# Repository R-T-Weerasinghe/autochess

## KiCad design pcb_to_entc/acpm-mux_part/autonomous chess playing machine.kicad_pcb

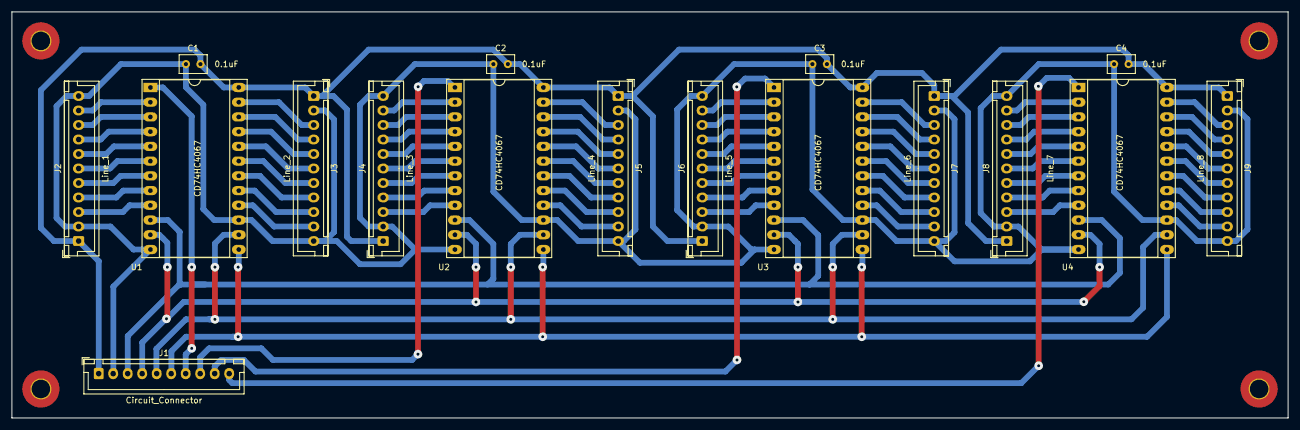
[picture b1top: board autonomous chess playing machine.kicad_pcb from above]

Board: 2 copper layers, 220.0 x 70.0 mm, 17 parts (0 on the bottom side), 74 nets.

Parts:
C1, C2, C3, C4: 0.1uF; C_Rect_L4.6mm_W3.0mm_P2.50mm_MKS02_FKP02
J1: Circuit_Connector; JST_XH_B10B-XH-A_1x10_P2.50mm_Vertical
J2: Line_1; JST_XH_B11B-XH-A_1x11_P2.50mm_Vertical
J3: Line_2; JST_XH_B11B-XH-A_1x11_P2.50mm_Vertical
J4: Line_3; JST_XH_B11B-XH-A_1x11_P2.50mm_Vertical
J5: Line_4; JST_XH_B11B-XH-A_1x11_P2.50mm_Vertical
J6: Line_5; JST_XH_B11B-XH-A_1x11_P2.50mm_Vertical
J7: Line_6; JST_XH_B11B-XH-A_1x11_P2.50mm_Vertical
J8: Line_7; JST_XH_B11B-XH-A_1x11_P2.50mm_Vertical
J9: Line_8; JST_XH_B11B-XH-A_1x11_P2.50mm_Vertical
U1, U2, U3, U4: CD74HC4067; DIP-24_W15.24mm_Socket_LongPads

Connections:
/Ground: C1.1, C2.1, C3.1, C4.1, J1.2, J2.2, J2.11, J3.2, J3.11, J4.2, J4.11, J5.2, J5.11, J6.2, J6.11, J7.2, J7.11, J8.2, J8.11, J9.2, J9.11, U1.12 (GND), U1.15 (~E), U2.12 (GND), U2.15 (~E), U3.12 (GND), U3.15 (~E), U4.12 (GND), U4.15 (~E)
unnamed: C1.2, C2.2, C3.2, C4.2, J1.1, J2.1, J3.1, J4.1, J5.1, J6.1, J7.1, J8.1, J9.1, U1.24 (VCC), U2.24 (VCC), U3.24 (VCC), U4.24 (VCC)
unnamed: J1.3, U1.10 (S0), U2.10 (S0), U3.10 (S0), U4.10 (S0)
unnamed: J1.4, U1.11 (S1), U2.11 (S1), U3.11 (S1), U4.11 (S1)
unnamed: J1.5, U1.14 (S2), U2.14 (S2), U3.14 (S2), U4.14 (S2)
unnamed: J1.6, U1.13 (S3), U2.13 (S3), U3.13 (S3), U4.13 (S3)
unnamed: J1.7, U1.1 (COM)
unnamed: J1.8, U2.1 (COM)
unnamed: J1.9, U3.1 (COM)
unnamed: J1.10, U4.1 (COM)
unnamed: J2.3, U1.9 (I0)
unnamed: J2.4, U1.8 (I1)
unnamed: J2.5, U1.7 (I2)
unnamed: J2.6, U1.6 (I3)
unnamed: J2.7, U1.5 (I4)
unnamed: J2.8, U1.4 (I5)
unnamed: J2.9, U1.3 (I6)
unnamed: J2.10, U1.2 (I7)
unnamed: J3.3, U1.23 (I8)
unnamed: J3.4, U1.22 (I9)
unnamed: J3.5, U1.21 (I10)
unnamed: J3.6, U1.20 (I11)
unnamed: J3.7, U1.19 (I12)
unnamed: J3.8, U1.18 (I13)
unnamed: J3.9, U1.17 (I14)
unnamed: J3.10, U1.16 (I15)
unnamed: J4.3, U2.9 (I0)
unnamed: J4.4, U2.8 (I1)
unnamed: J4.5, U2.7 (I2)
unnamed: J4.6, U2.6 (I3)
unnamed: J4.7, U2.5 (I4)
unnamed: J4.8, U2.4 (I5)
unnamed: J4.9, U2.3 (I6)
unnamed: J4.10, U2.2 (I7)
unnamed: J5.3, U2.23 (I8)
unnamed: J5.4, U2.22 (I9)
unnamed: J5.5, U2.21 (I10)
unnamed: J5.6, U2.20 (I11)
unnamed: J5.7, U2.19 (I12)
unnamed: J5.8, U2.18 (I13)
unnamed: J5.9, U2.17 (I14)
unnamed: J5.10, U2.16 (I15)
unnamed: J6.3, U3.9 (I0)
unnamed: J6.4, U3.8 (I1)
unnamed: J6.5, U3.7 (I2)
unnamed: J6.6, U3.6 (I3)
unnamed: J6.7, U3.5 (I4)
unnamed: J6.8, U3.4 (I5)
unnamed: J6.9, U3.3 (I6)
unnamed: J6.10, U3.2 (I7)
unnamed: J7.3, U3.23 (I8)
unnamed: J7.4, U3.22 (I9)
unnamed: J7.5, U3.21 (I10)
unnamed: J7.6, U3.20 (I11)
unnamed: J7.7, U3.19 (I12)
unnamed: J7.8, U3.18 (I13)
unnamed: J7.9, U3.17 (I14)
unnamed: J7.10, U3.16 (I15)
unnamed: J8.3, U4.9 (I0)
unnamed: J8.4, U4.8 (I1)
unnamed: J8.5, U4.7 (I2)
unnamed: J8.6, U4.6 (I3)
unnamed: J8.7, U4.5 (I4)
unnamed: J8.8, U4.4 (I5)
unnamed: J8.9, U4.3 (I6)
unnamed: J8.10, U4.2 (I7)
unnamed: J9.3, U4.23 (I8)
unnamed: J9.4, U4.22 (I9)
unnamed: J9.5, U4.21 (I10)
unnamed: J9.6, U4.20 (I11)
unnamed: J9.7, U4.19 (I12)
unnamed: J9.8, U4.18 (I13)
unnamed: J9.9, U4.17 (I14)
unnamed: J9.10, U4.16 (I15)

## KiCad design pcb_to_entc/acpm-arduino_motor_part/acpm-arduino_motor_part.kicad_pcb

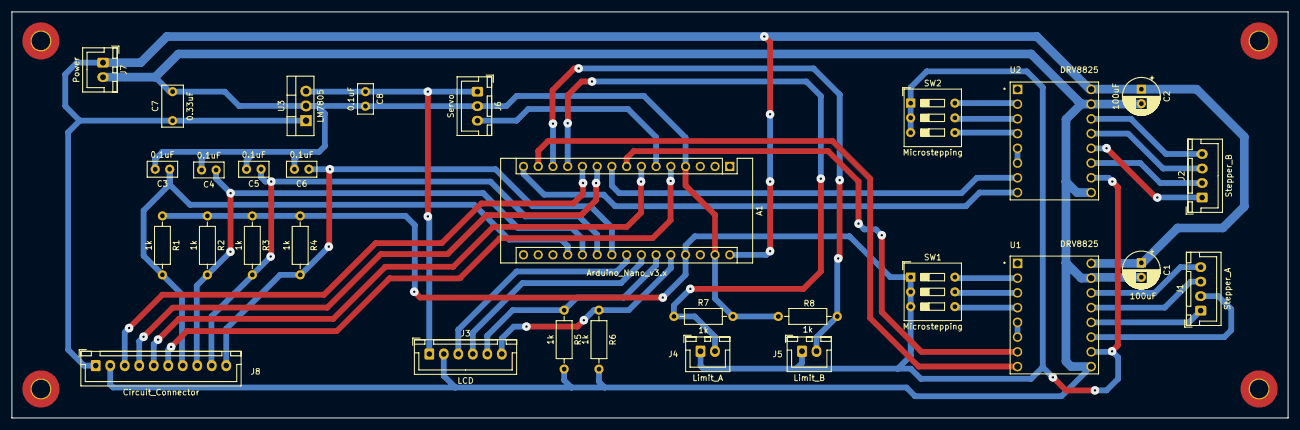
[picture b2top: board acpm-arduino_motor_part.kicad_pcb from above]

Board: 2 copper layers, 220.0 x 70.0 mm, 30 parts (0 on the bottom side), 39 nets.

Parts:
A1: Arduino_Nano_v3.x; Arduino_Nano
C1, C2: 100uF; CP_Radial_D6.3mm_P2.50mm
C3, C4, C5, C6, C8: 0.1uF; C_Disc_D5.0mm_W2.5mm_P2.50mm
C7: 0.33uF; C_Rect_L7.0mm_W3.5mm_P5.00mm
J1: Stepper_A; JST_XH_B4B-XH-A_1x04_P2.50mm_Vertical
J2: Stepper_B; JST_XH_B4B-XH-A_1x04_P2.50mm_Vertical
J3: LCD; JST_XH_B6B-XH-A_1x06_P2.50mm_Vertical
J4: Limit_A; JST_XH_B2B-XH-A_1x02_P2.50mm_Vertical
J5: Limit_B; JST_XH_B2B-XH-A_1x02_P2.50mm_Vertical
J6: Servo; JST_XH_B3B-XH-A_1x03_P2.50mm_Vertical
J7: Power; JST_XH_B2B-XH-A_1x02_P2.50mm_Vertical
J8: Circuit_Connector; JST_XH_B10B-XH-A_1x10_P2.50mm_Vertical
R1, R2, R3, R4, R5, R6, R7, R8: 1k; R_Axial_DIN0207_L6.3mm_D2.5mm_P10.16mm_Horizontal
SW1, SW2: Microstepping; SW_DIP_SPSTx03_Slide_9.78x9.8mm_W7.62mm_P2.54mm
U1, U2: DRV8825; IC_DRV8825_STEPPER_MOTOR_DRIVER_CARRIER
U3: LM7805; TO-220-3_Vertical

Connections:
/12V: A1.30 (VIN), C1.1, C2.1, C7.1, J7.1, J8.1, U1.16 (VMOT), U2.16 (VMOT), U3.1 (VI)
/GND: A1.4 (GND), A1.29 (GND), C1.2, C2.2, C3.2, C4.2, C5.2, C6.2, C7.2, C8.2, J3.2, J6.2, J7.2, J8.2, R5.2, R6.2, R7.2, R8.2, U1.9 (GND), U1.15 (GND_MOT), U2.9 (GND), U2.15 (GND_MOT), U3.2 (GND)
/SCL: A1.24 (A5), J3.4
/SDA: A1.23 (A4), J3.3
/SW1: A1.25 (A6), J3.5, R5.1
/SW2: A1.26 (A7), J3.6, R6.1
/Sig: A1.6 (D3), J6.3
unnamed: A1.5 (D2), J8.6
unnamed: A1.7 (D4), J8.5
unnamed: A1.8 (D5), U1.7 (STEP)
unnamed: A1.9 (D6), U2.7 (STEP)
unnamed: A1.10 (D7), J8.4
unnamed: A1.11 (D8), J8.3
unnamed: A1.12 (D9), J4.2, R7.1
unnamed: A1.13 (D10), J5.2, R8.1
unnamed: A1.14 (D11), U1.8 (DIR)
unnamed: A1.15 (D12), U2.8 (DIR)
unnamed: A1.19 (A0), C3.1, J8.7, R1.2
unnamed: A1.20 (A1), C4.1, J8.8, R2.2
unnamed: A1.21 (A2), C5.1, J8.9, R3.2
unnamed: A1.22 (A3), C6.1, J8.10, R4.2
unnamed: A1.27 (+5V), J4.1, J5.1, R1.1, R2.1, R3.1, R4.1, SW1.1, SW1.2, SW1.3, SW2.1, SW2.2, SW2.3, U1.10 (~FLT), U2.10 (~FLT)
unnamed: C8.1, J3.1, J6.1, U3.3 (VO)
unnamed: J1.1, U1.12 (A1)
unnamed: J1.2, U1.11 (A2)
unnamed: J1.3, U1.13 (B1)
unnamed: J1.4, U1.14 (B2)
unnamed: J2.1, U2.12 (A1)
unnamed: J2.2, U2.11 (A2)
unnamed: J2.3, U2.13 (B1)
unnamed: J2.4, U2.14 (B2)
unnamed: SW1.4, U1.4 (M2)
unnamed: SW1.5, U1.3 (M1)
unnamed: SW1.6, U1.2 (M0)
unnamed: SW2.4, U2.4 (M2)
unnamed: SW2.5, U2.3 (M1)
unnamed: SW2.6, U2.2 (M0)
unnamed: U1.5 (~RST), U1.6 (~SLP)
unnamed: U2.5 (~RST), U2.6 (~SLP)

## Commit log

2024-08-31 added files
